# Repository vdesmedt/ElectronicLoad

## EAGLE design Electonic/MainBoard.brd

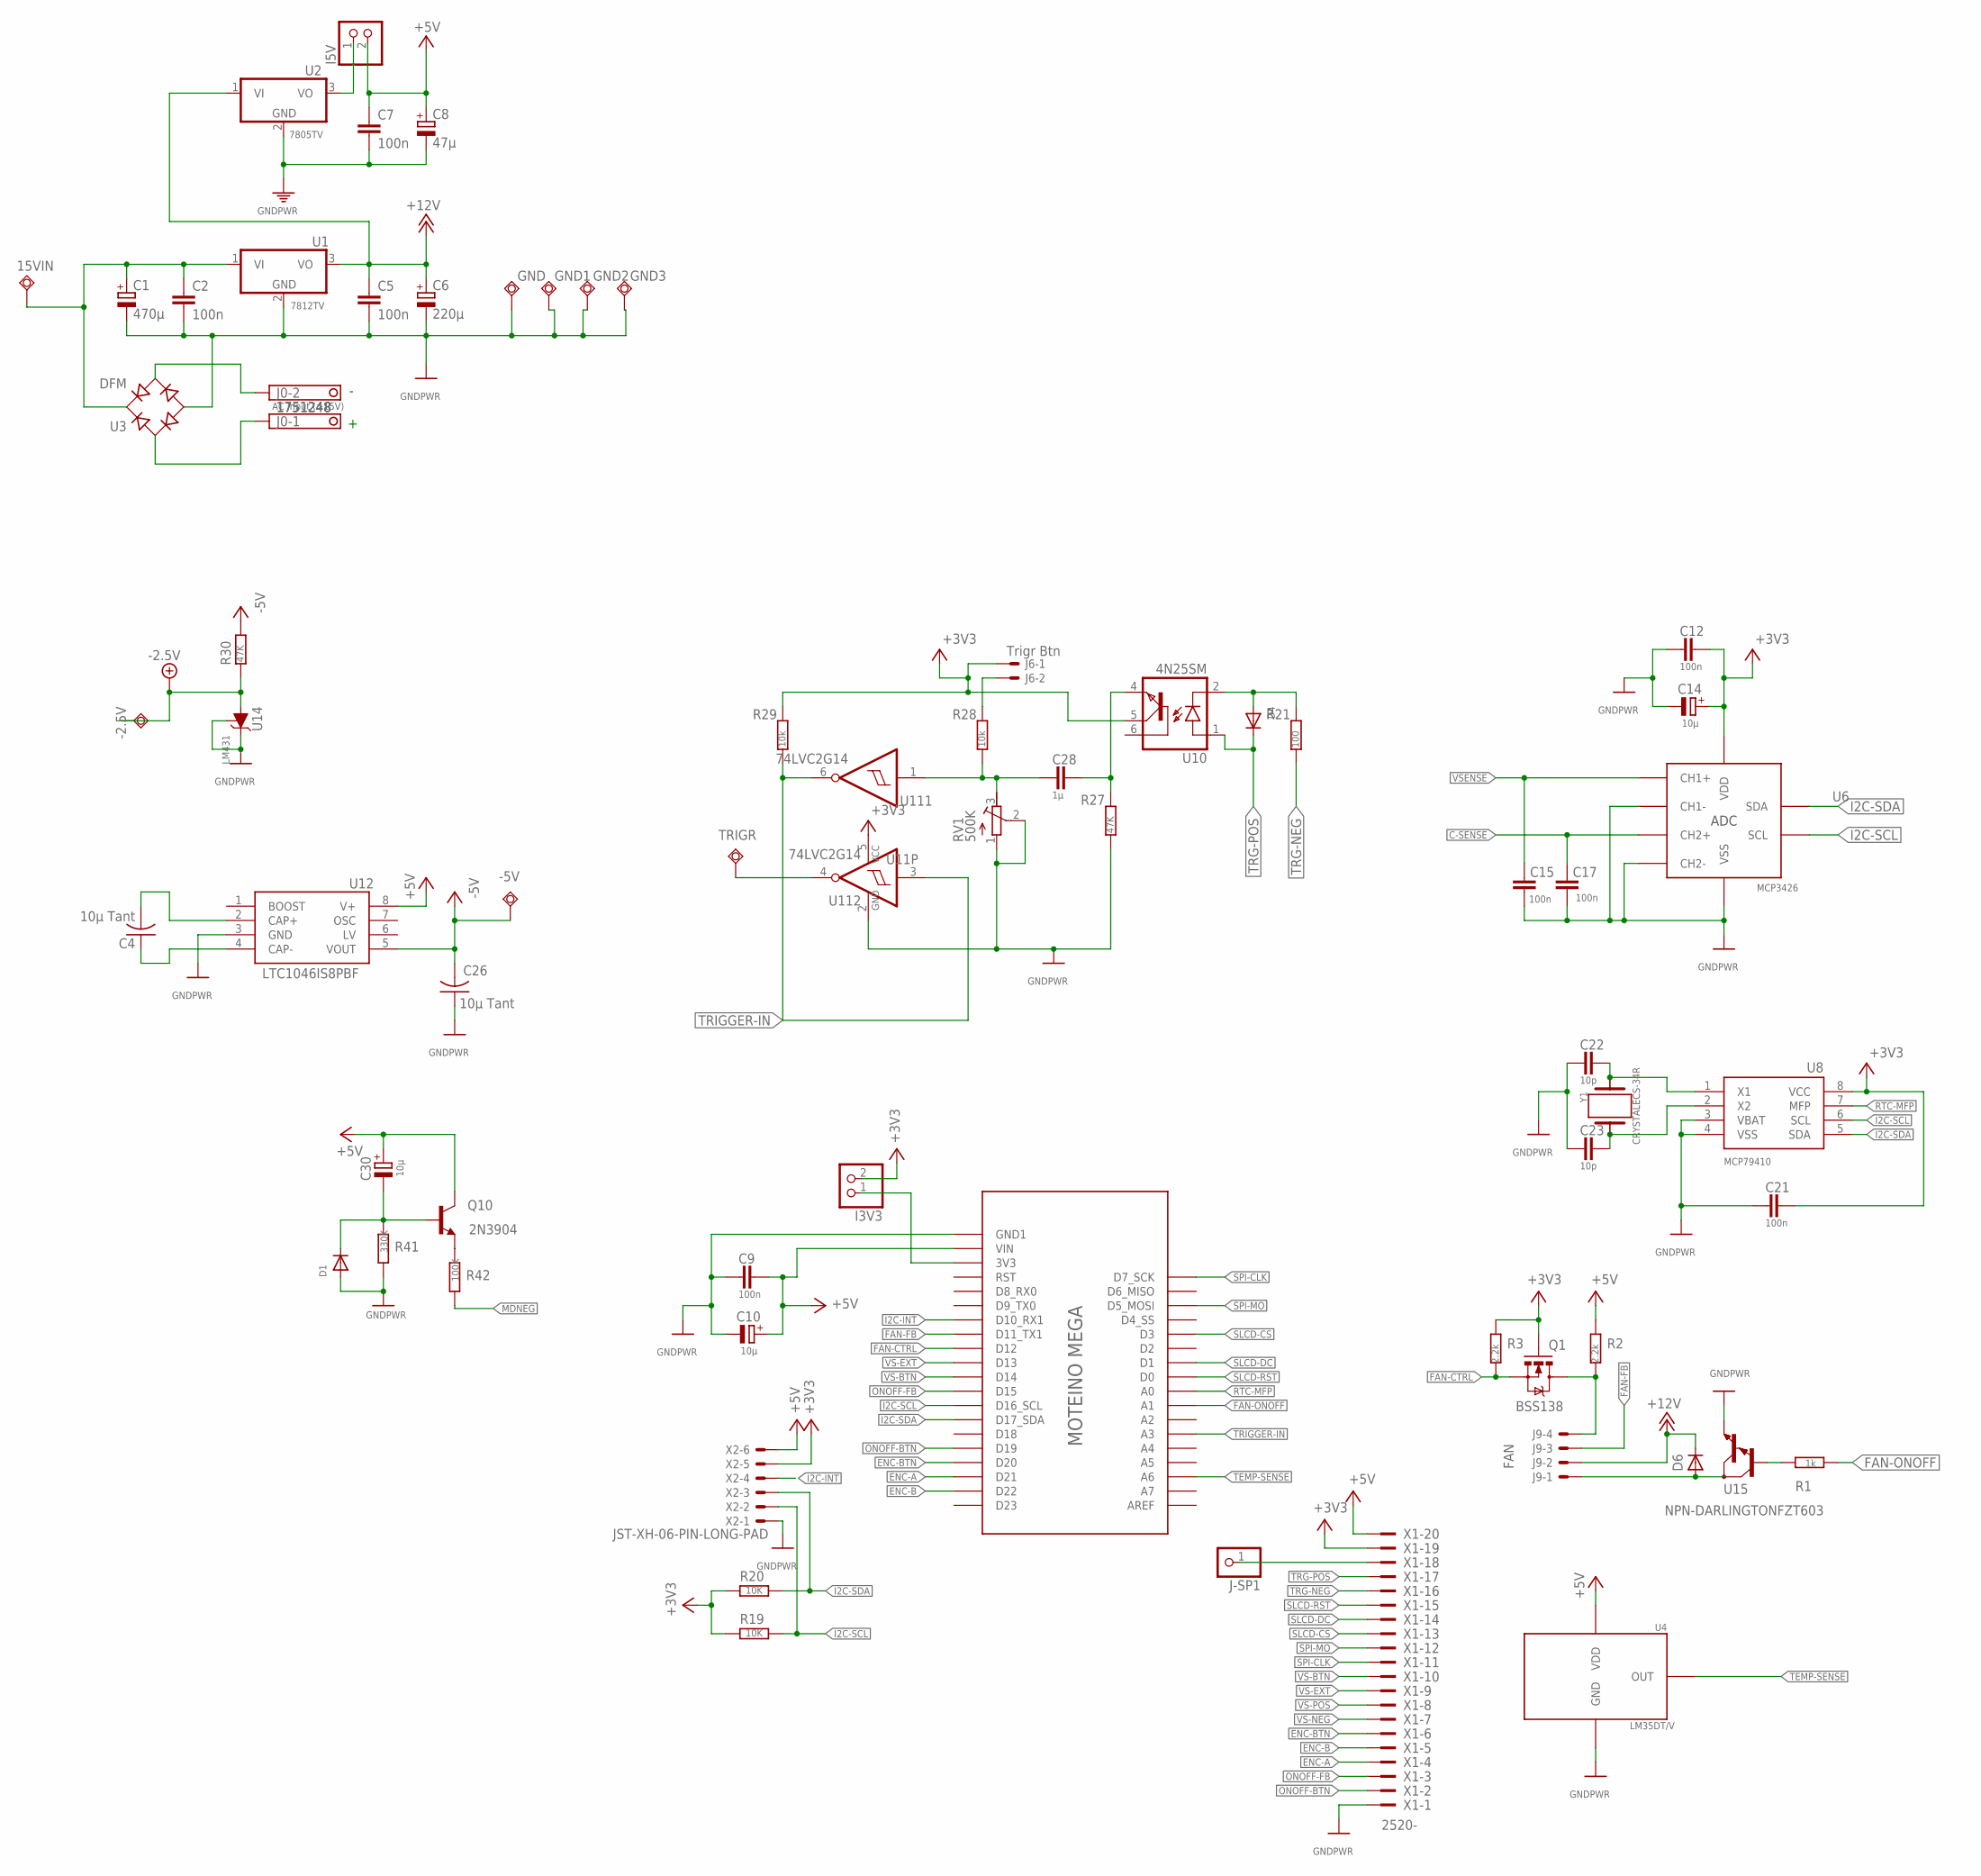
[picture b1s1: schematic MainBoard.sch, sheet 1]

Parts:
15VIN: TEST-POINT4952; TP-KEYSTONE-4952
-2.5V, -5V: TEST-POINT4952; TP-KEYSTONE-4952
C1: 470µ; E5-10,5
C2, C5, C7, C9, C12, C15, C17, C21: 100n; C0805K
C4, C26: 10µ Tant; C1210
C6: 220µ; E5-10,5
C8: 47µ; E5-5
C10, C14, C30: 10µ; E2-5
C22, C23: 10p; C0805K
C28: 1µ; C0805K
D1, D4: DIODESOD-323F; SOD-323F
D6: DIODE_SOD-123FL; SOD-123FL
GND, GND1, GND2, GND3: TEST-POINT4952; TP-KEYSTONE-4952
I3V3, I5V: PINHD-1X2; 1X02
J0: 1751248
J6: Trigr Btn; JST-XH-02-PACKAGE-ROUND-PAD
J9: FAN; JST-XH-04-PACKAGE-ROUND-PAD
J-SP1: PINHD-1X1; 1X01
Q1: BSS138; SOT23
Q10: 2N3904; TO92
R1: 1k; R0805
R2, R3: 2.2k; R0805
R19, R20: 10K; R0805
R21: 100; R0805
R27, R30: 47K; R0805
R28, R29: 10k; R0805
R41: 330K; R0805
R42: 100K; R0805
RV1: 500K; RTRIM3296W
TRIGR: TEST-POINT4952; TP-KEYSTONE-4952
U1: 7812TV; TO220V
U2: 7805TV; TO220V
U3: DFM
U4: LM35DT/V; TO220V
U6: MCP3426; SO8
U8: MCP79410; SOIC127P600X175-8N
U10: 4N25SM; DIL6-SMD
U11: 74LVC2G14; SOT23-6
U12: LTC1046IS8PBF; SOIC127P599X175-8N
U14: LM431; SOT23
U15: NPN-DARLINGTONFZT603; SOT223
U$1: MOTEINO_MEGA_SIMPLE
X1: 2520-; PAK100/2500-20
X2: JST-XH-06-PIN-LONG-PAD; JST-XH-06-PACKAGE-LONG-PAD
Y1: CRYSTALECS-34R; ECS32712534RRTR

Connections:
+3V3: C12.1, C14.+, C21.1, I3V3.2, J6.1, Q1.1 (G), R3.2, R19.2, R20.2, R29.2, U6.3 (VDD), U8.8 (VCC), U10.5 (COL), U11.5 (VCC), X1.19, X2.5
+5V: C7.1, C8.+, C9.1, C10.+, C30.+, I5V.2, Q10.1 (C), R2.2, U4.1 (VDD), U12.8 (V+), U$1.VIN, U$1.VIN_2 (VIN), X1.20, X2.6; also elsewhere on the board
+12V: C5.1, C6.+, D6.C, J9.2, U1.3 (VO), U2.1 (VI)
-2.5V: -2.5V.P$1, R30.1, U14.3 (A); also elsewhere on the board
-5V: -5V.P$1, C26.2, R30.2, U12.5 (VOUT); also elsewhere on the board
C-SENSE: C17.2, U6.7 (CH2+); also elsewhere on the board
ENC-A: U$1.D21, X1.4
ENC-B: U$1.D22, X1.5
ENC-BTN: U$1.D20, X1.6
FAN-CTRL: Q1.2 (S), R3.1, U$1.D12
FAN-CTRL-5V: J9.4, Q1.3 (D), R2.1
FAN-FB: J9.3, U$1.D11 (D11_TX1)
FAN-ONOFF: R1.1, U$1.A1
GND: C1.-, C2.2, C5.2, C6.-, C7.2, C8.-, C9.2, C10.-, C12.2, C14.-, C15.2, C17.1, C21.2, C22.2, C23.2, C26.1, D1.A, GND.P$1, GND1.P$1, GND2.P$1, GND3.P$1, R27.1, R41.2, RV1.1 (A), RV1.2 (S), U1.2 (GND), U2.2 (GND), U3.-, U4.2 (GND), U6.2 (CH1-), U6.6 (VSS), U6.8 (CH2-), U8.3 (VBAT), U8.4 (VSS), U11.2 (GND), U12.3 (GND), U14.1 (C), U14.2 (ADJ), U15.3 (E), U$1.GND1, U$1.GND_2 (GND1), X1.1, X2.1; also elsewhere on the board
I2C-INT: U$1.D10 (D10_RX1), X2.4
I2C-SCL: R19.1, U6.5 (SCL), U8.6 (SCL), U$1.D16 (D16_SCL), X2.2; also elsewhere on the board
I2C-SDA: R20.1, U6.4 (SDA), U8.5 (SDA), U$1.D17 (D17_SDA), X2.3; also elsewhere on the board
MDNEG: R42.2; also elsewhere on the board
unnamed: TRIGR.P$1, U11.4 (O)
unnamed: D6.A, J9.1, U15.2 (C), U15.4 (C)
unnamed: I5V.1, U2.3 (VO)
unnamed: I3V3.1, U$1.3V3, U$1.3V3_2 (3V3)
unnamed: 15VIN.P$1, C1.+, C2.1, U1.1 (VI), U3.+
unnamed: J0.1, U3.A1 (AC1)
unnamed: J0.2, U3.A2 (AC2)
unnamed: C4.2, U12.2 (CAP+)
unnamed: J-SP1.1, X1.18
unnamed: C4.1, U12.4 (CAP-)
unnamed: C28.2, R28.1, RV1.3 (E), U11.1 (I)
unnamed: C28.1, R27.2, U10.4 (EMI)
unnamed: D4.A, R21.2, U10.2 (C)
unnamed: J6.2, R28.2
unnamed: Q10.3 (E), R42.1
unnamed: C30.-, D1.C, Q10.2 (B), R41.1
ONOFF-BTN: U$1.D19, X1.2
ONOFF-FB: U$1.D15, X1.3
RTC-MFP: U8.7 (MFP), U$1.A0
RTCX1: C22.1, U8.1 (X1), Y1.1
RTCX2: C23.1, U8.2 (X2), Y1.2
SLCD-CS: U$1.D3, X1.13
SLCD-DC: U$1.D1, X1.14
SLCD-RST: U$1.D0, X1.15
SPI-CLK: U$1.D7 (D7_SCK), X1.11
SPI-MO: U$1.D5 (D5_MOSI), X1.12
TEMP-SENSE: U4.3 (OUT), U$1.A6
TRG-NEG: R21.1, X1.16
TRG-POS: D4.C, U10.1 (A), X1.17
TRIGGER-IN: R29.1, U11.3 (I), U11.6 (O), U$1.A3
U15IN: R1.2, U15.1 (B)
VS-BTN: U$1.D14, X1.10
VS-EXT: U$1.D13, X1.9
VS-NEG: X1.7; also elsewhere on the board
VS-POS: X1.8; also elsewhere on the board
VSENSE: C15.1, U6.1 (CH1+); also elsewhere on the board

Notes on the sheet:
AC Input (>15V)

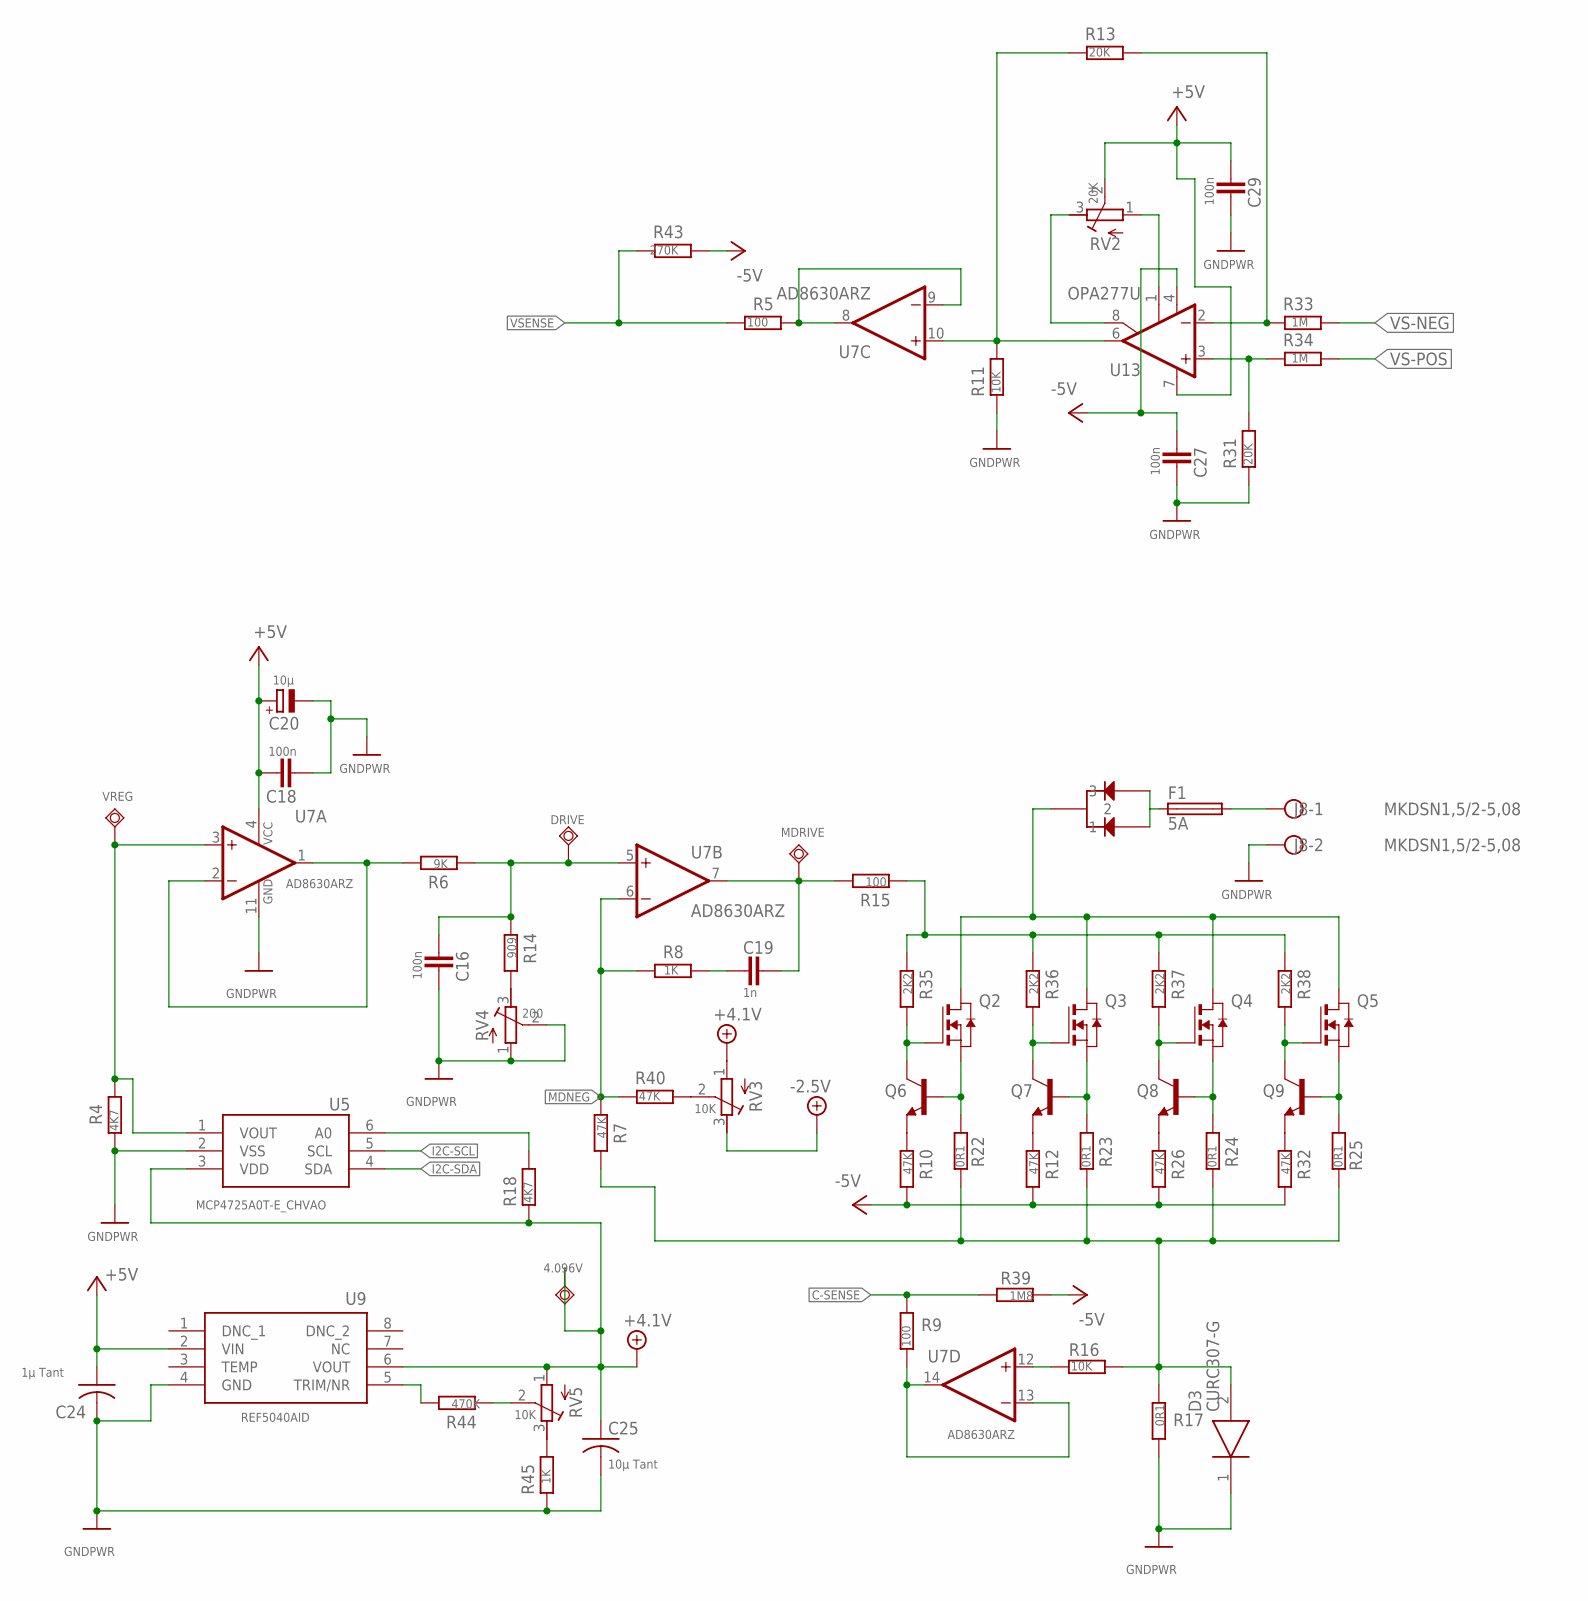
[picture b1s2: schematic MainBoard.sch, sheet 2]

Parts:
4.096V: TEST-POINT4952; TP-KEYSTONE-4952
C16, C18, C27, C29: 100n; C0805K
C19: 1n; C0805K
C20: 10µ; E2-5
C24: 1µ Tant; C1210
C25: 10µ Tant; C1210
D3: CURC307-G; DIOM7959X262N
D5: MBR41H100CT/V; TO220-VERT
DRIVE: TEST-POINT4952; TP-KEYSTONE-4952
F1: 5A; SHK20L
J8: MKDSN1,5/2-5,08
MDRIVE: TEST-POINT4952; TP-KEYSTONE-4952
Q2, Q3, Q4, Q5: SUP70040E/V; TO220-VERT
Q6, Q7, Q8, Q9: MPS2222A-NPN-TO92-CBE; TO92-CBE
R4, R18: 4K7; R0805
R5, R9, R15: 100; R0805
R6: 9K; R0805
R7, R10, R12, R26, R32: 47K; R0805
R8, R45: 1K; R0805
R11, R16: 10K; R0805
R13, R31: 20K; R1206
R14: 909; R1206
R17: 0R1; TO220-DPAC
R22, R23, R24, R25: 0R1; 0750V
R33, R34: 1M; R1206
R35, R36, R37, R38: 2K2; R0805
R39: 1M8; R0805
R40: 47K; R1206
R43: 270K; R0805
R44: 470K; R0805
RV2: 20K; RTRIM3296W
RV3, RV5: 10K; RTRIM3296W
RV4: 200; RTRIM3296W
U5: MCP4725A0T-E_CHVAO; SOT95P270X145-6N
U7: AD8630ARZ; SO14
U9: REF5040AID; SOIC127P600X175-8N
U13: OPA277U; SO08
VREG: TEST-POINT4952; TP-KEYSTONE-4952

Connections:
+4.1V: 4.096V.P$1, C25.1, R18.1, RV3.1 (A), RV5.1 (A), U5.3 (VDD), U9.6 (VOUT)
+5V: C18.1, C20.+, C24.1, C29.2, RV2.2 (S), U7.4 (VCC), U9.2 (VIN), U13.7 (V+); also elsewhere on the board
-2.5V: RV3.3 (E); also elsewhere on the board
-5V: C27.2, R10.2, R12.2, R26.2, R32.2, R39.1, R43.2, U13.4 (V-); also elsewhere on the board
C-SENSE: R9.2, R39.2; also elsewhere on the board
DACA0: R18.2, U5.6 (A0)
DACVO: R4.2, U5.1 (VOUT), U7.3 (+IN), VREG.P$1
GND: C16.1, C18.2, C20.-, C24.2, C25.2, C27.1, C29.1, D3.1 (K), J8.2, R4.1, R11.1, R17.2, R31.1, R45.1, RV4.1 (A), RV4.2 (S), U5.2 (VSS), U7.11 (GND), U9.4 (GND); also elsewhere on the board
I2C-SCL: U5.5 (SCL); also elsewhere on the board
I2C-SDA: U5.4 (SDA); also elsewhere on the board
MDNEG: R7.1, R8.1, R40.1, U7.6 (-IN); also elsewhere on the board
unnamed: R44.2, U9.5 (TRIM/NR)
unnamed: R45.2, RV5.3 (E)
unnamed: R44.1, RV5.2 (S)
unnamed: R6.2, U7.1 (OUT), U7.2 (-IN)
unnamed: C16.2, DRIVE.P$1, R6.1, R14.1, U7.5 (+IN)
unnamed: R13.2, R33.1, U13.2 (-IN)
unnamed: R14.2, RV4.3 (E)
unnamed: C19.1, MDRIVE.P$1, R15.2, U7.7 (OUT)
unnamed: Q2.1 (G), Q6.C, R35.2
unnamed: C19.2, R8.2
unnamed: Q3.1 (G), Q7.C, R36.2
unnamed: Q4.1 (G), Q8.C, R37.2
unnamed: Q5.1 (G), Q9.C, R38.2
unnamed: R15.1, R35.1, R36.1, R37.1, R38.1
unnamed: Q6.E, R10.1
unnamed: Q7.E, R12.1
unnamed: Q8.E, R26.1
unnamed: Q2.3 (S), Q6.B, R22.2
unnamed: Q9.E, R32.1
unnamed: Q3.3 (S), Q7.B, R23.2
unnamed: Q4.3 (S), Q8.B, R24.2
unnamed: Q5.3 (S), Q9.B, R25.2
unnamed: R40.2, RV3.2 (S)
unnamed: D3.2 (A), R7.2, R16.2, R17.1, R22.1, R23.1, R24.1, R25.1
unnamed: D5.2, Q2.2 (D), Q3.2 (D), Q4.2 (D), Q5.2 (D)
unnamed: R16.1, U7.12 (+IN)
unnamed: R9.1, U7.13 (-IN), U7.14 (OUT)
unnamed: D5.1, D5.3, F1.1A (1), F1.1B (1)
unnamed: F1.2A (2), F1.2B (2), J8.1
unnamed: R31.2, R34.1, U13.3 (+IN)
unnamed: RV2.3 (E), U13.8 (CMP2)
unnamed: RV2.1 (A), U13.1 (CMP1)
unnamed: R5.2, U7.8 (OUT), U7.9 (-IN)
U13-O: R11.2, R13.1, U7.10 (+IN), U13.6 (OUT)
VS-NEG: R33.2; also elsewhere on the board
VS-POS: R34.2; also elsewhere on the board
VSENSE: R5.1, R43.1; also elsewhere on the board

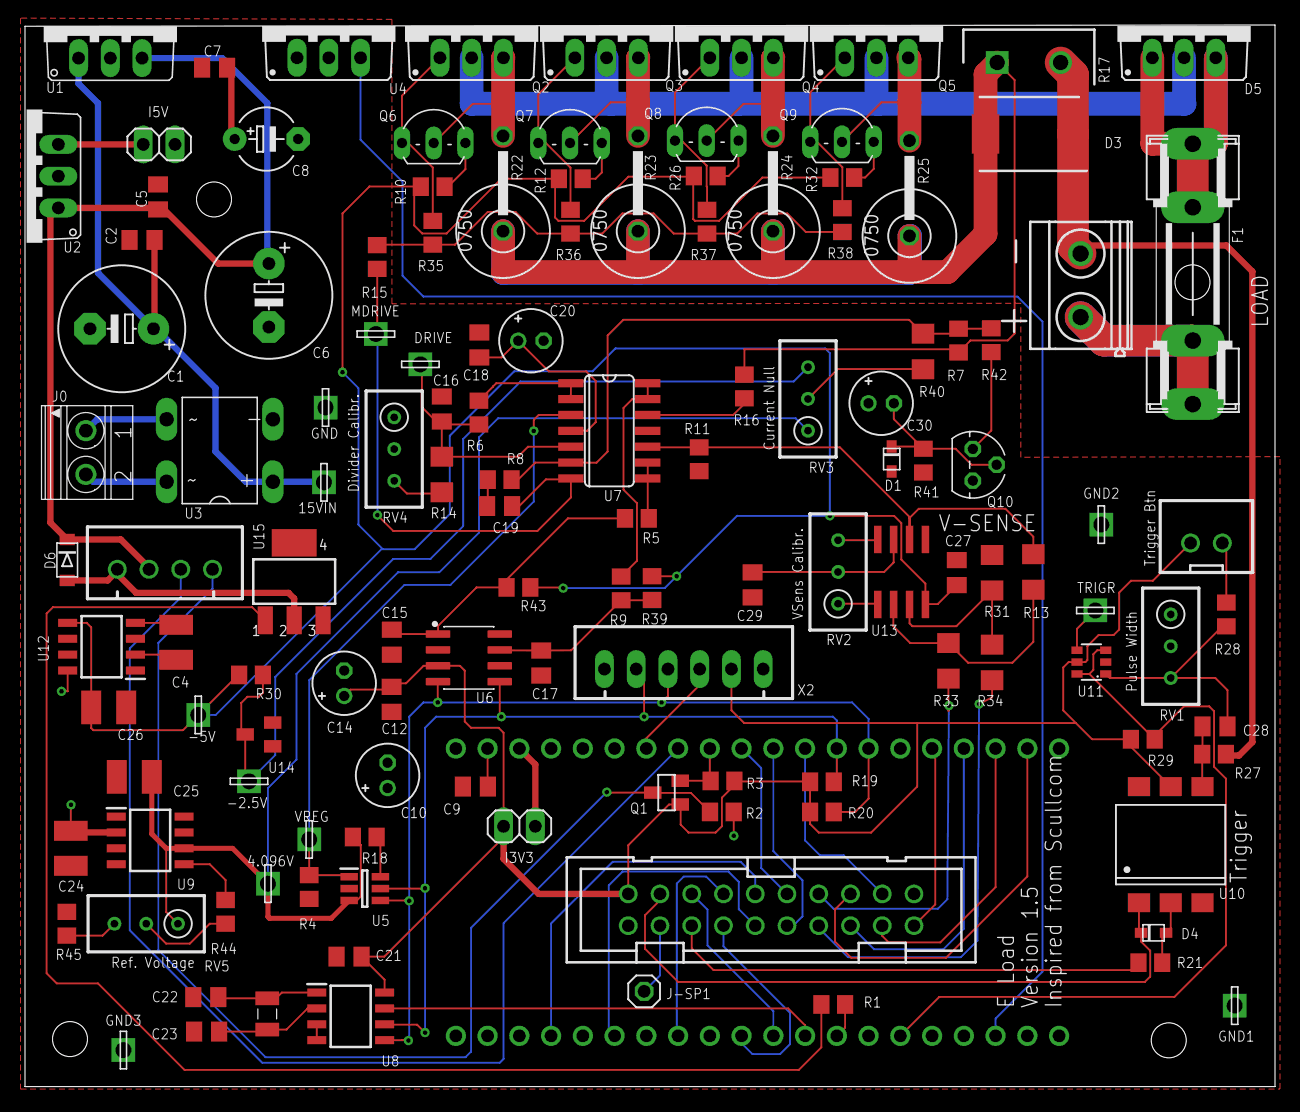
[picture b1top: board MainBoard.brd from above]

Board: 2 copper layers, 100.0 x 84.9 mm, 131 parts (1 on the bottom side), 91 nets.

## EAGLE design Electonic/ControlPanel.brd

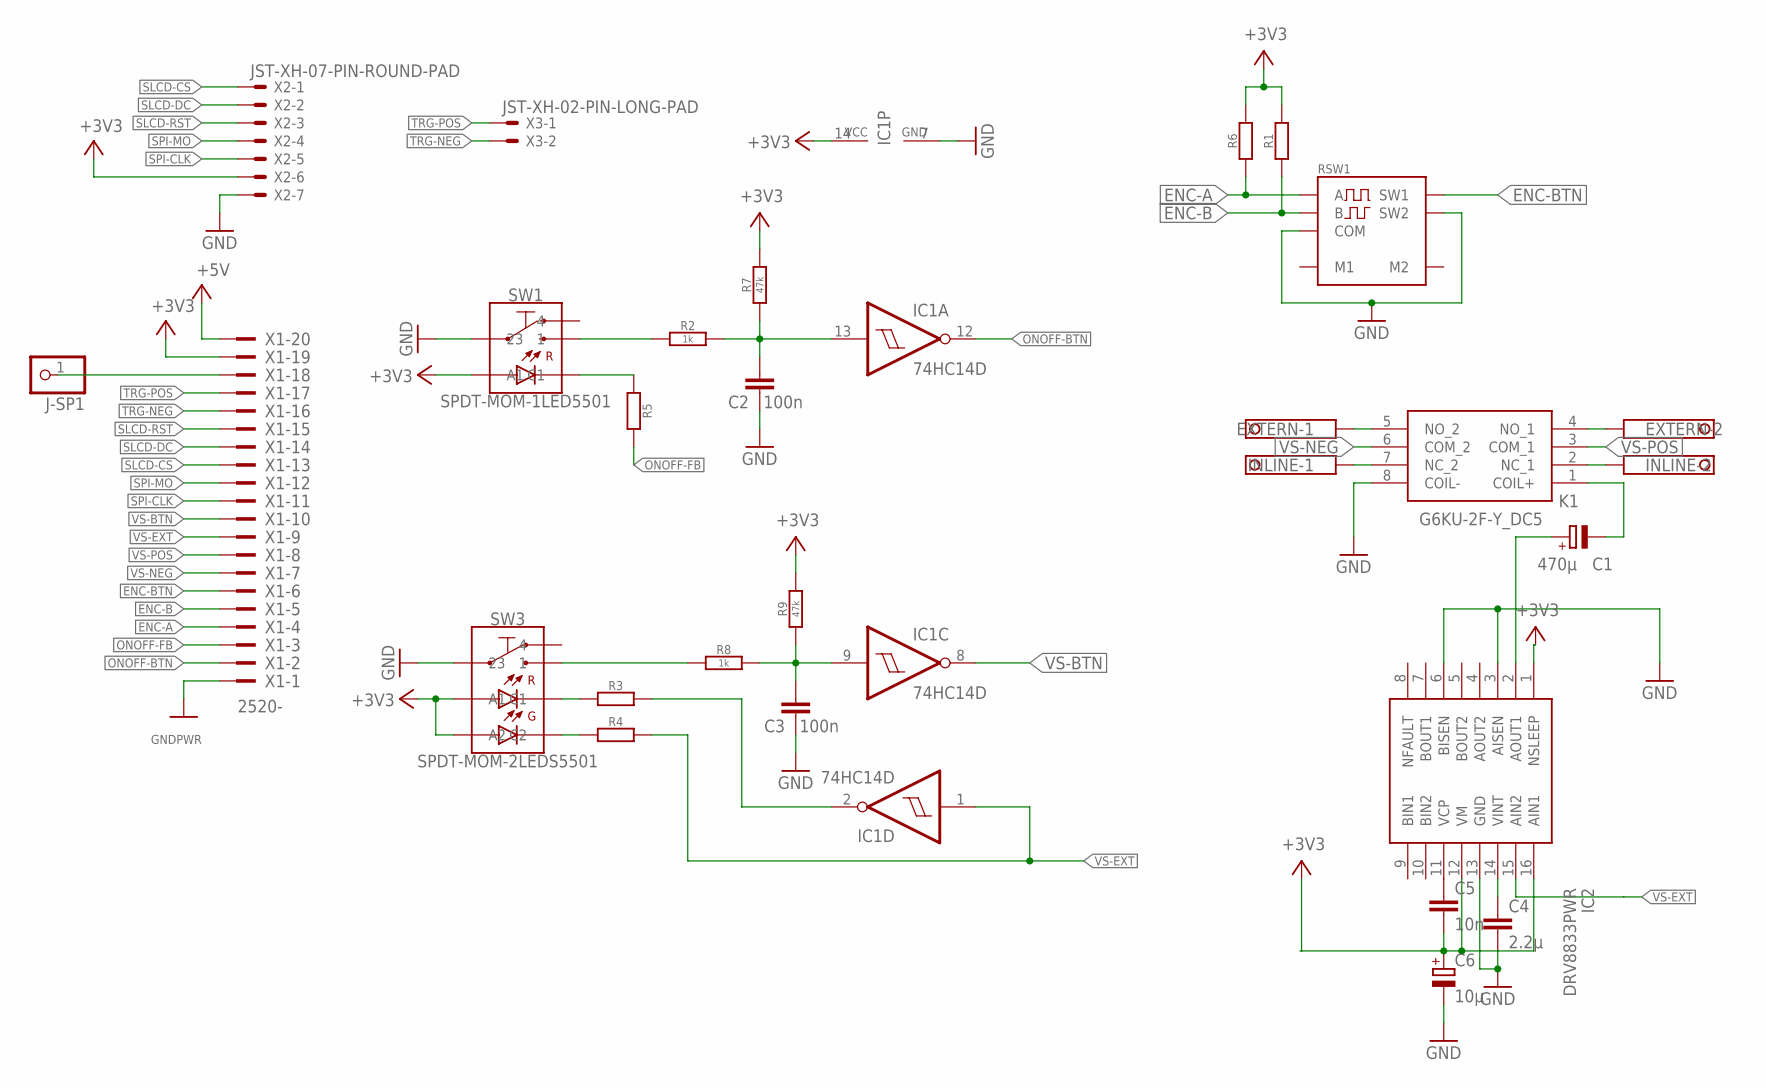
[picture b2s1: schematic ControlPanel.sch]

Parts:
C1: 470µ; E5-10,5
C2, C3: 100n; 0805
C4: 2.2µ; 0805
C5: 10n; 0805
C6: 10µ; E2-5
EXTERN: 1751248
IC1: 74HC14D; SO14
IC2: DRV8833PWR; SOP65P640X120-16N
INLINE: 1751248
J-SP1: PINHD-1X1; 1X01
K1: G6KU-2F-Y_DC5; G6KU2FYDC5
R1, R3, R4, R5, R6: RESISTOR1206; 1206
R2, R8: 1k; 0805
R7, R9: 47k; 0805
RSW1: SW-EC11E; EC11E
SW1: SPDT-MOM-1LED5501; 5501-BTN-1LED
SW3: SPDT-MOM-2LEDS5501; 5501-BTN-2LEDS
X1: 2520-; PAK100/2500-20
X2: JST-XH-07-PIN-ROUND-PAD; JST-XH-07-PACKAGE-ROUND-PAD
X3: JST-XH-02-PIN-LONG-PAD; JST-XH-02-PACKAGE-LONG-PAD

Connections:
+3V3: C5.2, C6.+, IC1.14 (VCC), IC2.1 (NSLEEP), IC2.12 (VM), IC2.16 (AIN1), R1.2, R6.2, R7.2, R9.2, SW1.5 (A1), SW3.5 (A1), SW3.8 (A2), X1.19, X2.6
+5V: X1.20
ENC-A: R6.1, RSW1.A, X1.4
ENC-B: R1.1, RSW1.B, X1.5
ENC-BTN: RSW1.SW1, X1.6
GND: C2.1, C3.1, C4.2, C6.-, IC1.7 (GND), IC2.3 (AISEN), IC2.6 (BISEN), IC2.13 (GND), K1.8 (COIL-), RSW1.C (COM), RSW1.SW2, SW1.2 (23), SW1.3 (23), SW3.2 (23), SW3.3 (23), X1.1, X2.7
unnamed: R8.1, SW3.1
unnamed: EXTERN.1, K1.5 (NO_2)
unnamed: R5.1, SW1.8 (C1)
unnamed: R2.1, SW1.1
unnamed: R4.1, SW3.7 (C2)
unnamed: R3.1, SW3.6 (C1)
unnamed: INLINE.1, K1.7 (NC_2)
unnamed: C2.2, IC1.13 (I), R2.2, R7.1
unnamed: INLINE.2, K1.2 (NC_1)
unnamed: EXTERN.2, K1.4 (NO_1)
unnamed: C1.-, K1.1 (COIL+)
unnamed: C1.+, IC2.2 (AOUT1)
unnamed: C4.1, IC2.14 (VINT)
unnamed: C3.2, IC1.9 (I), R8.2, R9.1
unnamed: C5.1, IC2.11 (VCP)
unnamed: J-SP1.1, X1.18
ONOFF-BTN: IC1.12 (O), X1.2
ONOFF-FB: R5.2, X1.3
SLCD-CS: X1.13, X2.1
SLCD-DC: X1.14, X2.2
SLCD-RST: X1.15, X2.3
SPI-CLK: X1.11, X2.5
SPI-MO: X1.12, X2.4
TRG-NEG: X1.16, X3.2
TRG-POS: X1.17, X3.1
V-INL: IC1.2 (O), R3.2
VS-BTN: IC1.8 (O), X1.10
VS-EXT: IC1.1 (I), IC2.15 (AIN2), R4.2, X1.9
VS-NEG: K1.6 (COM_2), X1.7
VS-POS: K1.3 (COM_1), X1.8

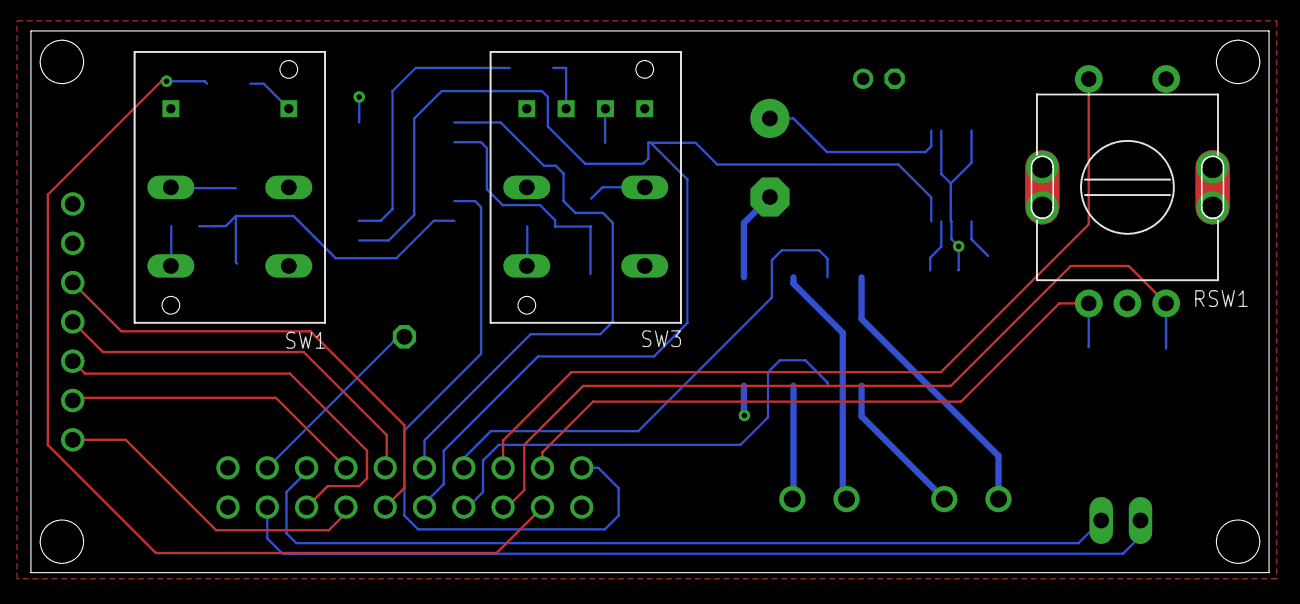
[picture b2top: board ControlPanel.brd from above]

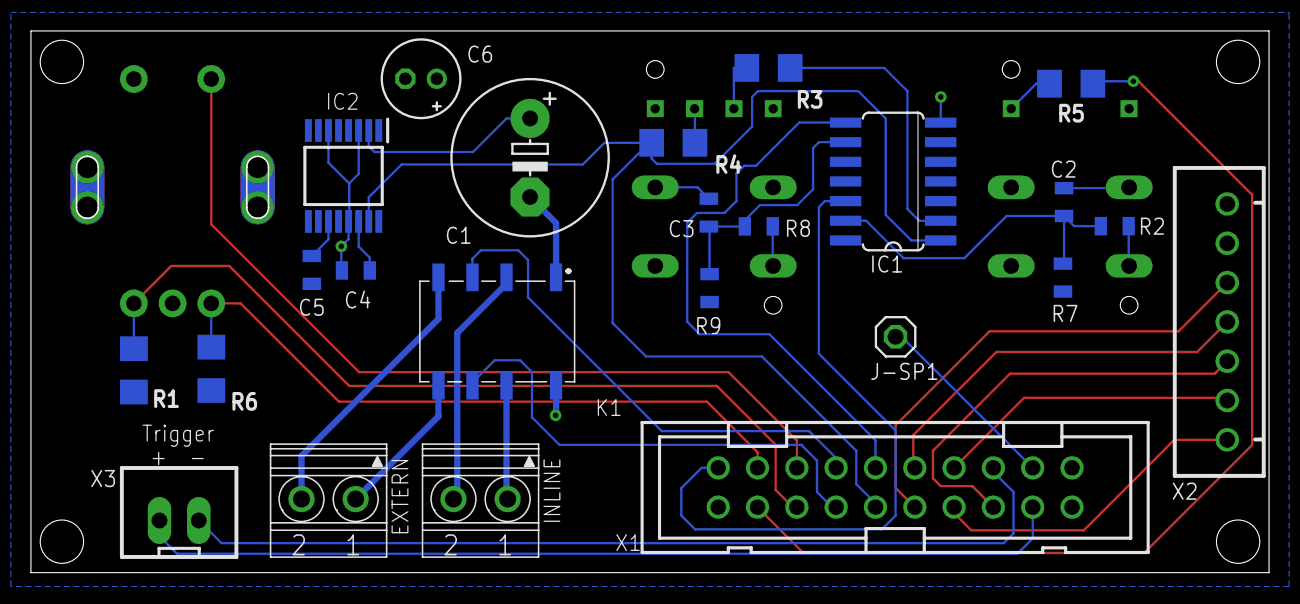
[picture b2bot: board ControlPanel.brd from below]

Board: 2 copper layers, 79.9 x 34.9 mm, 27 parts (24 on the bottom side), 35 nets.

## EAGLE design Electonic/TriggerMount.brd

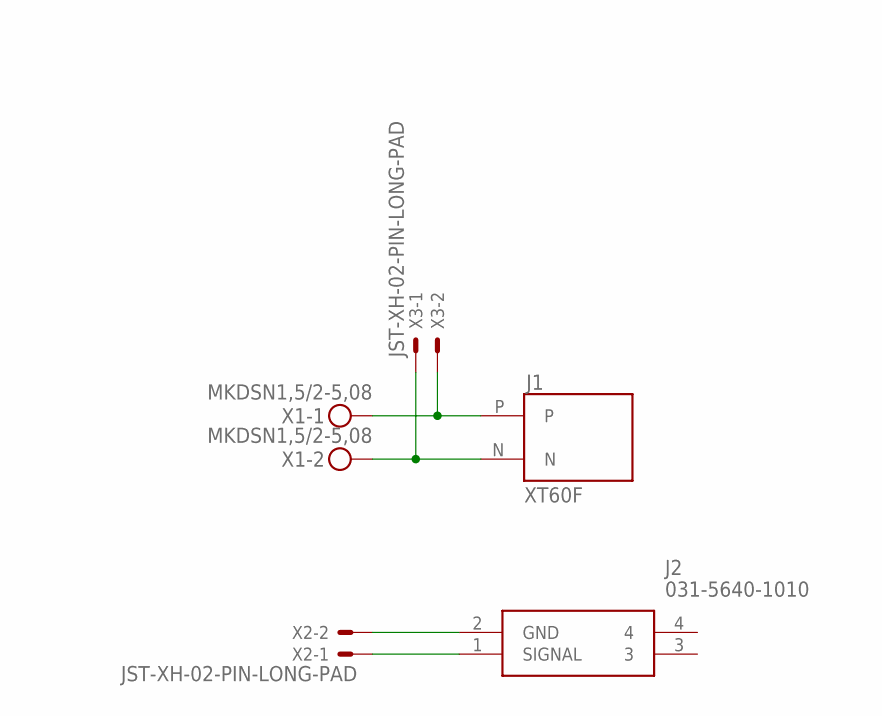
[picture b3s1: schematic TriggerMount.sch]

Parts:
J1: XT60F; XT60PW
J2: 031-5640-1010; 03156401010
X1: MKDSN1,5/2-5,08
X2, X3: JST-XH-02-PIN-LONG-PAD; JST-XH-02-PACKAGE-LONG-PAD

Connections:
unnamed: J1.N, X1.2, X3.1
unnamed: J1.P, X1.1, X3.2
unnamed: J2.2 (GND), X2.2
unnamed: J2.1 (SIGNAL), X2.1

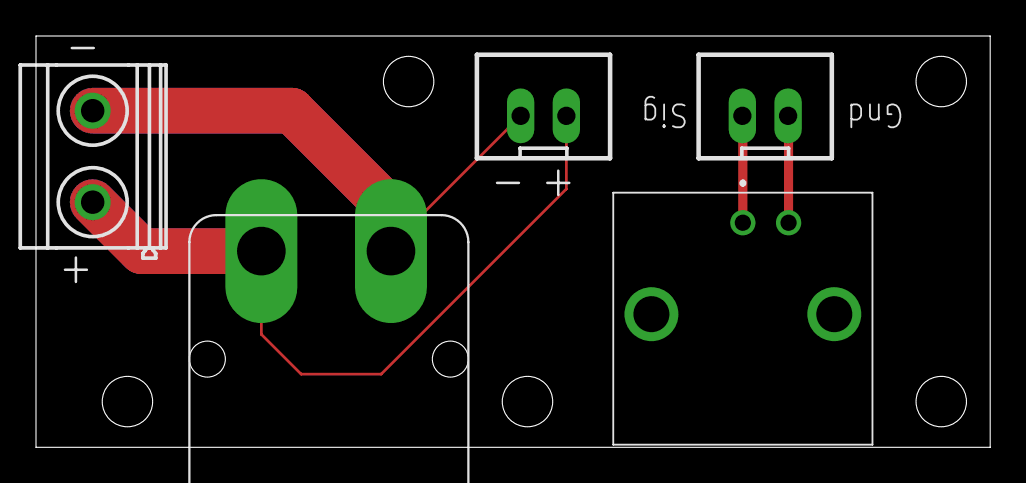
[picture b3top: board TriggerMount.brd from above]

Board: 2 copper layers, 53.0 x 22.9 mm, 5 parts (0 on the bottom side), 4 nets.

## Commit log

2020-05-09 MovingAvergae on temperature
2020-05-09 Two level fan speed with Hysteresis
2020-05-09 Optimize Display speed
2020-05-09 Fix current reading
2020-05-09 Added Test RTC & IO Expender
2020-05-10 Optimize EncoderButton timings
2020-05-10 Optimize Reding display frequency
2020-05-10 Fan Speed Icon
2020-05-10 Fixed DAC Value
2020-05-15 Scrollable Menu
2020-05-16 Display issues with Current
2020-05-16 Switch off when changing mode
2020-05-17 debug
2020-05-17 remove enum MenuItemtype
2020-05-17 Setting to Flah
2020-05-17 Set DAC EEProm on first boot
2020-05-18 Trigger Pin Config
2020-05-18 Added Time and mAh
2020-05-18 BattCellCount + Code optimization and cleanup
2020-05-18 Optimize memory footprint (Special Chars)
2020-05-20 Code reorganisation step 1
2020-05-20 Distribution Class
2020-05-20 Memory Optimization
2020-05-20 MenuItem prefix in Flash MEM
2020-05-21 Add Trigger in Menu
2020-05-21 Display improvement
2020-05-21 Battery Curoff
2020-05-21 Fixed suspicious Batt Cell Count
2020-05-22 Only output available memory in debug
2020-05-22 Code organisation
2020-05-22 Logging Interval + Fan level
2020-05-22 Loggin INterval from 1 to 3600 included
2020-05-23 Logging Modes
2020-05-23 Triggers
2020-05-23 Only save when iddle & Off
2020-05-25 First trial to solve hidden menui item getting focus
2020-06-03 Added MCP0008
2020-09-15 Moved to Atmel1284 & SPI LCD
2020-09-16 Replace TimerOne with TimerOneThree to support Atmega1284 PWM on Pin12 (used by Timer1)
2020-09-16 Only setDACValue when changed or On/Off
2020-09-16 Fan fine tuning
2020-09-16 Remove old Fan Pin Number
2020-09-18 Updated Font
2020-09-18 Only consider hysteresis when temp goes down
2020-09-18 Update menu & display
2020-09-18 Display optimization
2020-09-18 Menu - focus timeout
2020-09-18 Added Alert popup & settings
2020-10-20 Mainboard V1.5 with VSense Button Connected
2020-10-20 Typo + extend R17 range
2020-10-20 Workspace edit
2020-11-04 Lxi over RFM69 Started
2020-11-04 Folder Reorg + Add Eagle Files
